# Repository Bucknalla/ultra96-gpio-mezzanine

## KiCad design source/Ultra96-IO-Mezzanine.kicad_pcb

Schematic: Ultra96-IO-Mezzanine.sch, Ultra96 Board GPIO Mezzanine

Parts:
C1, C3: 4.7uF; C_0805_2012Metric
C2, C4: 0.1uF; C_0805_2012Metric
C5, C6, C7, C9: 1uF; C_0805_2012Metric
C8: C_Small; C_0805_2012Metric
D1, D2, D8, D9, D10: LED; LED_0805_2012Metric
D3: SP0503BAHT; SOT-143
D4, D5, D6, D7: D_Schottky; D_0805_2012Metric
H1, H2: MountingHole; Hole_2.5MM
J1, J3: USB_C_Receptacle_USB2.0; USB_C_Receptacle_HRO_TYPE-C-31-M-12
J2: Conn_01x08_Female; PinHeader_1x08_P2.54mm_Vertical
P1: CONN_02X20; PinHeader_2x20_P2.54mm_Vertical
P2: CONN_02X30; 61083-063400LF
P3: CONN_02X20; Socket_Strip_SMD_2x20_Pitch2mm; Mfr Part # F240-1220A0xMUx1
Q1: STL6P3LLH6; TRANS_STL6P3LLH6
R1: 22.1K; R_0805_2012Metric
R2: 47.5K; R_0805_2012Metric
R3, R6, R9, R11, R12, R13: 1K; R_0805_2012Metric
R4, R5: 75R; R_0805_2012Metric
R7: 100K; R_0805_2012Metric
R8: 22K; R_0805_2012Metric
R10: 100; R_0805_2012Metric
SW1: SW_SP3T; SW_SP3T_PCM13
SW2: PWR_BTN; SW_Push_1P1T_NO_Vertical_Wuerth_434133025816
SW3: RST_BTN; SW_Push_1P1T_NO_Vertical_Wuerth_434133025816
U2: CP2102N-A01-GQFN24; QFN-24-1EP_4x4mm_P0.5mm_EP2.6x2.6mm
U3, U5, U6, U7: TXS0108EPW; QFN50P450X350X100-21N
U4: STUSB4500QTR; QFN-24-1EP_4x4mm_P0.5mm_EP2.7x2.7mm

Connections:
+1V8: P3.35, SW1.1, U3.2 (VCCA), U3.10 (OE), U5.2 (VCCA), U5.10 (OE), U6.2 (VCCA), U6.10 (OE), U7.2 (VCCA), U7.10 (OE); also elsewhere on the board
+2V8: C6.1, U4.23 (VREG_2V7)
+3V3: C3.1, C4.1, P1.1, P1.17, R3.1, R4.1, R5.1, R11.1, R12.1, R13.1, SW1.2, U2.5, U2.6, U4.22 (VSYS)
+5V: P1.2, P1.4, P3.37, SW1.4, U2.7; also elsewhere on the board
CC1: D7.1 (K), J1.A5 (CC1), U4.1 (CC1DB), U4.2 (CC1)
CC2: D5.1 (K), J1.B5 (CC2), U4.4 (CC2), U4.5 (CC2DB)
CLK0/CSI0_MCLK: P2.15
CLK1/CSI1_MCLK: P2.17
CSI0_C+: P2.2
CSI0_C-: P2.4
CSI0_D0+: P2.8
CSI0_D0-: P2.10
CSI0_D1+: P2.14
CSI0_D1-: P2.16
CSI0_D2+: P2.20
CSI0_D2-: P2.22
CSI0_D3+: P2.26
CSI0_D3-: P2.28
CSI1_C+: P2.54
CSI1_C-: P2.56
CSI1_D0+: P2.42
CSI1_D0-: P2.44
CSI1_D1+: P2.48
CSI1_D1-: P2.50
D+: D3.4, J3.A6 (D+), J3.B6 (D+), U2.3
D-: D3.3, J3.A7 (D-), J3.B7 (D-), U2.4
DSI_CLK+: P2.21
DSI_CLK-: P2.23
DSI_D0+: P2.27
DSI_D0-: P2.29
DSI_D1+: P2.33
DSI_D1-: P2.35
DSI_D2+: P2.39
DSI_D2-: P2.41
DSI_D3+: P2.45
DSI_D3-: P2.47
GND: C1.2, C2.2, C3.2, C4.2, C5.2, C6.2, C7.2, C9.2, D3.1, D4.2 (A), D5.2 (A), D6.2 (A), D7.2 (A), J1.A1 (GND), J1.A12 (GND), J1.B1 (GND), J1.B12 (GND), J1.S1 (SHIELD), J2.4, J3.A1 (GND), J3.A12 (GND), J3.B1 (GND), J3.B12 (GND), J3.S1 (SHIELD), P1.6, P1.9, P1.14, P1.20, P1.25, P1.30, P1.34, P1.39, P2.6, P2.12, P2.13, P2.18, P2.19, P2.24, P2.25, P2.30, P2.31, P2.37, P2.40, P2.43, P2.46, P2.49, P2.52, P2.55, P2.58, P3.1, P3.2, P3.39, P3.40, R2.1, SW2.1, SW3.1, U2.2, U2.25, U3.11 (GND), U4.10 (GND), U4.12 (ADDR0), U4.13 (ADDR1), U4.25 (GND), U5.11 (GND), U6.11 (GND), U7.11 (GND); also elsewhere on the board
GPIO_A: P3.23, U3.4 (A3); also elsewhere on the board
GPIO_A_RPI: P1.7, U3.17 (B3)
GPIO_B: P3.24, U7.3 (A2); also elsewhere on the board
GPIO_B_RPI: P1.32, U7.18 (B2)
GPIO_C: P3.25, U3.5 (A4); also elsewhere on the board
GPIO_C_RPI: P1.13, U3.16 (B4)
GPIO_D: P3.26, U3.6 (A5); also elsewhere on the board
GPIO_D_RPI: P1.15, U3.15 (B5)
GPIO_E: P3.27, U6.1 (A1); also elsewhere on the board
GPIO_E_RPI: P1.16, U6.20 (B1)
GPIO_F: P3.28, U6.7 (A6); also elsewhere on the board
GPIO_F_RPI: P1.18, U6.14 (B6)
GPIO_G: P3.29, U6.3 (A2); also elsewhere on the board
GPIO_G_RPI: P1.22, U6.18 (B2)
GPIO_H: P3.30, U6.6 (A5); also elsewhere on the board
GPIO_H_RPI: P1.26, U6.15 (B5)
GPIO_I: P3.31, U6.4 (A3); also elsewhere on the board
GPIO_I_RPI: J2.5, P1.29, U6.17 (B3)
GPIO_J: P3.32, U5.4 (A3); also elsewhere on the board
GPIO_J_RPI: J2.6, P1.31, U5.17 (B3)
GPIO_K: P3.33, U6.5 (A4); also elsewhere on the board
GPIO_K_RPI: J2.8, P1.37, U6.16 (B4)
GPIO_L: P3.34, U5.5 (A4); also elsewhere on the board
GPIO_L_RPI: J2.7, P1.33, U5.16 (B4)
HSIC_STR: P2.57
I2C0_SCL: P3.15, U3.3 (A2); also elsewhere on the board
I2C0_SCL_RPI: J2.1, P1.5, U3.18 (B2), U4.7 (SCL)
I2C0_SDA: P3.17, U3.1 (A1); also elsewhere on the board
I2C0_SDA_RPI: J2.2, P1.3, U3.20 (B1), U4.8 (SDA)
I2C1_SCL: P3.19, U5.3 (A2); also elsewhere on the board
I2C1_SCL_RPI: P1.28, U5.18 (B2)
I2C1_SDA: P3.21, U5.1 (A1); also elsewhere on the board
I2C1_SDA_RPI: P1.27, U5.20 (B1)
I2C2_SCL: P2.32
I2C2_SDA: P2.34
I2C3_SCL: P2.36
I2C3_SDA: P2.38
unnamed: C7.1, U4.21 (VREG_1V2)
unnamed: C8.2, R10.1
unnamed: D1.1, U2.14
unnamed: D1.2, R5.2
unnamed: D2.1, U2.13
unnamed: D2.2, R4.2
unnamed: D8.1, U4.15 (GPIO)
unnamed: D8.2, R11.2
unnamed: D9.1, U4.20 (POWER_OK2)
unnamed: D9.2, R12.2
unnamed: D10.1, U4.14 (POWER_OK3)
unnamed: D10.2, R13.2
unnamed: Q1.1, Q1.2, Q1.3, R7.1
unnamed: Q1.4, R7.2, R8.1, R10.2
unnamed: R1.2, R2.2, U2.8
unnamed: R3.2, U2.9
unnamed: R6.1, U4.18 (VBUS_VS_DISCH)
unnamed: R8.2, U4.16 (VBUS_EN_SNK)
unnamed: R9.2, U4.9 (DISCH)
PCM_CLK: P3.18, U5.9 (A8); also elsewhere on the board
PCM_CLK_RPI: P1.12, U5.12 (B8)
PCM_DI: P3.22, U5.7 (A6); also elsewhere on the board
PCM_DI_RPI: P1.38, U5.14 (B6)
PCM_DO: P3.20, U5.8 (A7); also elsewhere on the board
PCM_DO_RPI: P1.40, U5.13 (B7)
PCM_FS: P3.16, U5.6 (A5); also elsewhere on the board
PCM_FS_RPI: P1.35, U5.15 (B5)
PWR_BTN_N: P3.4, SW2.2; also elsewhere on the board
RST_BTN_N: P3.6, SW3.2; also elsewhere on the board
SD_CMD/SPI1_DIN: P2.11
SD_DAT0/SPI1_DOUT: P2.1
SD_DAT1: P2.3
SD_DAT2: P2.5
SD_DAT3/SPI1_CS: P2.7
SD_SCLK/SPI1_SCLK: P2.9
SPIO_CS: P3.12, U7.1 (A1); also elsewhere on the board
SPIO_CS_RPI: P1.24, U7.20 (B1)
SPIO_DIN: P3.10, U3.8 (A7); also elsewhere on the board
SPIO_DIN_RPI: P1.21, U3.13 (B7)
SPIO_DOUT: P3.14, U3.7 (A6); also elsewhere on the board
SPIO_DOUT_RPI: P1.19, U3.14 (B6)
SPIO_SCL: P3.8, U3.9 (A8); also elsewhere on the board
SPIO_SCL_RPI: P1.23, U3.12 (B8)
SYS_DCIN: C8.1, D4.1 (K), P3.36, P3.38, Q1.5_8, R9.1; also elsewhere on the board
UART0_CTS: P3.3, U7.6 (A5); also elsewhere on the board
UART0_CTS_O: U2.19, U7.15 (B5)
UART0_RTS: P3.9, U7.7 (A6); also elsewhere on the board
UART0_RTS_O: U2.18, U7.14 (B6)
UART0_RX: P3.7, U7.5 (A4); also elsewhere on the board
UART0_RX_O: U2.21, U7.16 (B4)
UART0_TX: P3.5, U7.4 (A3); also elsewhere on the board
UART0_TX_O: U2.20, U7.17 (B3)
UART1_RX: P3.13, U6.9 (A8); also elsewhere on the board
UART1_RX_RPI: P1.10, U6.12 (B8)
UART1_TX: P3.11, U6.8 (A7); also elsewhere on the board
UART1_TX_RPI: P1.8, U6.13 (B7)
USB_D+: P2.51
USB_D-: P2.53
VBUS: C1.1, C2.1, D3.2, J3.A4 (VBUS), J3.A9 (VBUS), J3.B4 (VBUS), J3.B9 (VBUS), R1.1
VBUS_PWR: C5.1, C9.1, D6.1 (K), J1.A4 (VBUS), J1.A9 (VBUS), J1.B4 (VBUS), J1.B9 (VBUS), R6.2, U4.24 (VDD)
VCCB: J2.3, SW1.3, U3.19 (VCCB), U5.19 (VCCB), U6.19 (VCCB), U7.19 (VCCB)

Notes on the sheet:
Top Side Socket Strip
Bottom Side HS Connector
RPi Header
Level Shifters
Power Rails
Lepton Header
Voltage Toggle
USB PD
USB to UART Converter
Buttons
USB PD Connector
USB to Uart Connector

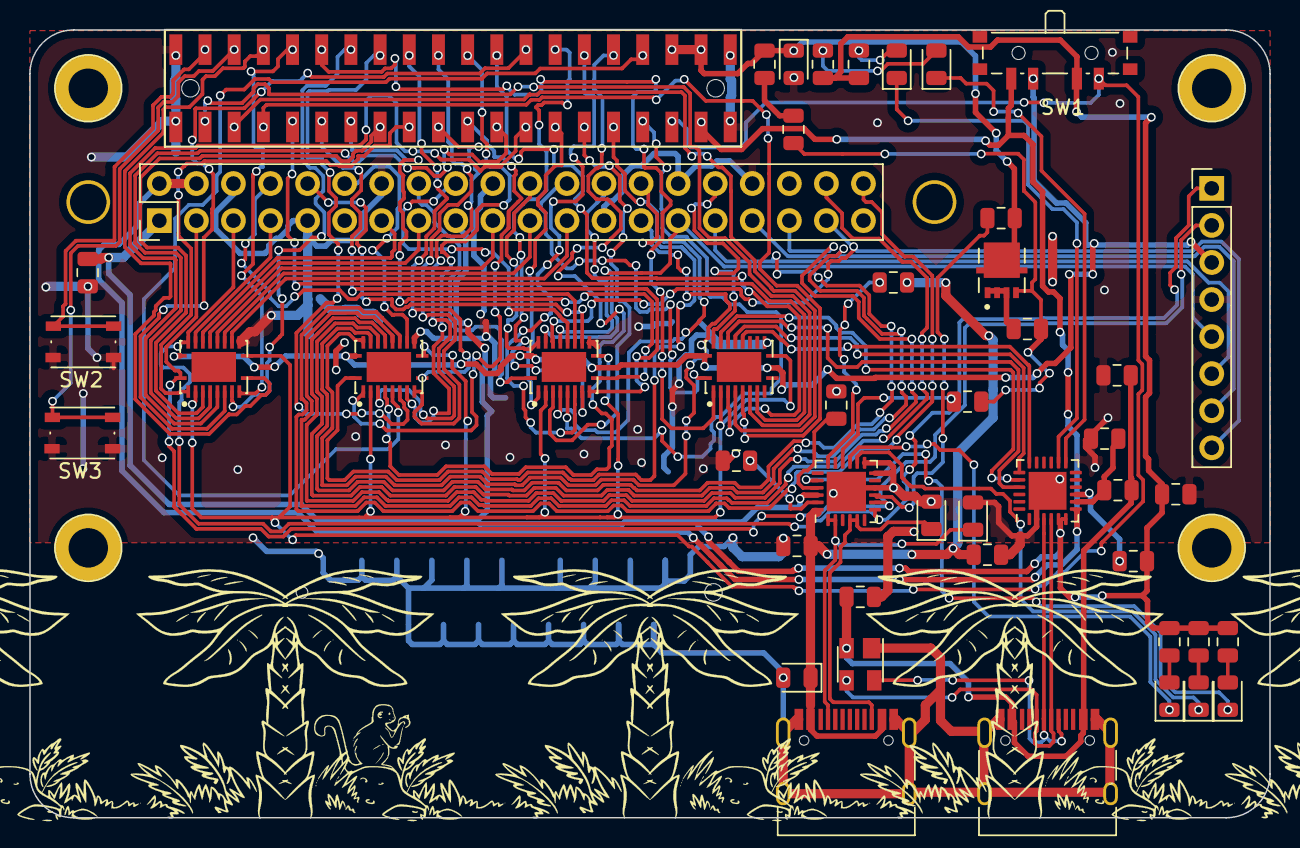
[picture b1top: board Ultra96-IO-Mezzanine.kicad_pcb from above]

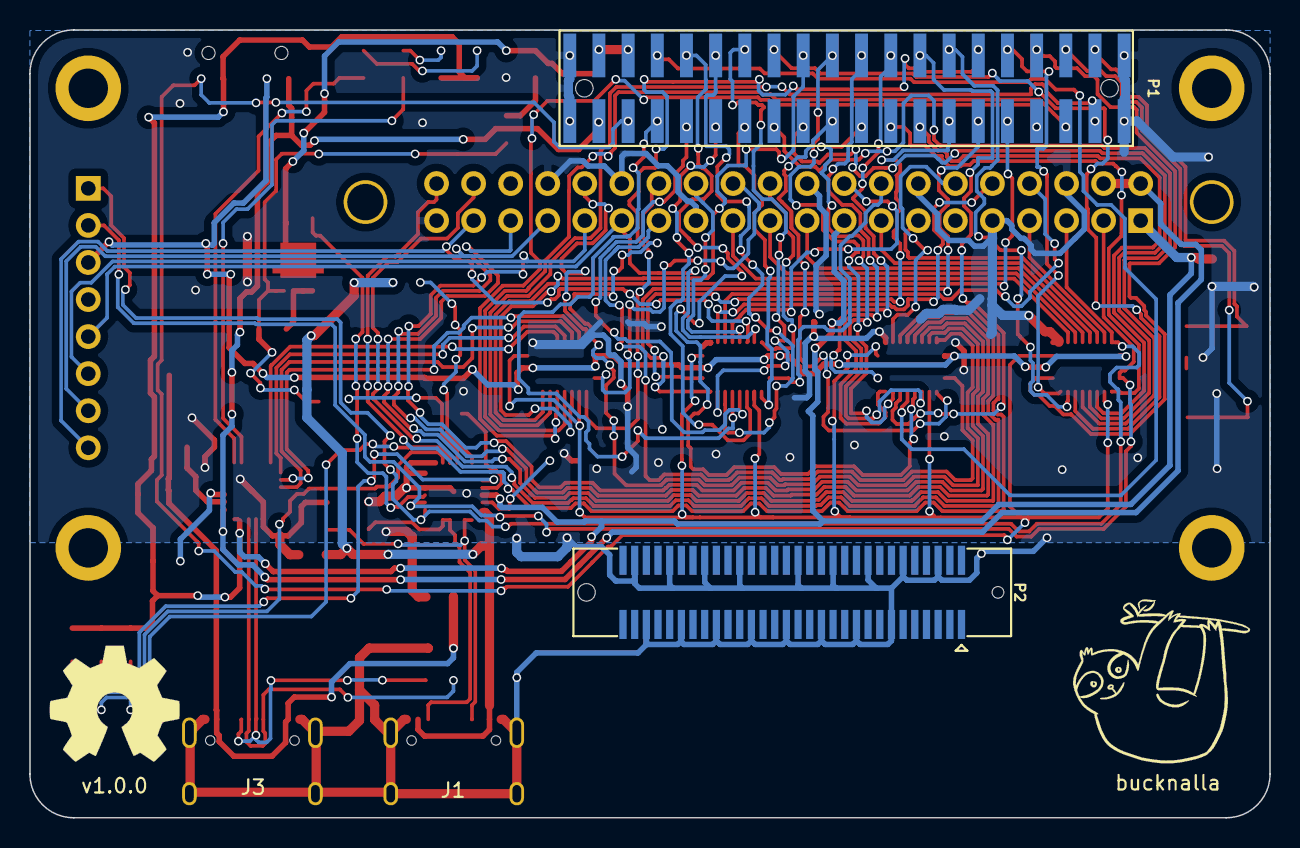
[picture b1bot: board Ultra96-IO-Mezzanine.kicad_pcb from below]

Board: 2 copper layers, 85.0 x 54.0 mm, 51 parts (2 on the bottom side), 94 nets.

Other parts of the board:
P1#2: CONN_02X20; Pin_Header_SMD_2x20_Pitch2mm

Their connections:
+1V8: P1#2.35; also elsewhere on the board
+5V: P1#2.37; also elsewhere on the board
GND: P1#2.1, P1#2.2, P1#2.39, P1#2.40; also elsewhere on the board
GPIO_A: P1#2.23; also elsewhere on the board
GPIO_B: P1#2.24; also elsewhere on the board
GPIO_C: P1#2.25; also elsewhere on the board
GPIO_D: P1#2.26; also elsewhere on the board
GPIO_E: P1#2.27; also elsewhere on the board
GPIO_F: P1#2.28; also elsewhere on the board
GPIO_G: P1#2.29; also elsewhere on the board
GPIO_H: P1#2.30; also elsewhere on the board
GPIO_I: P1#2.31; also elsewhere on the board
GPIO_J: P1#2.32; also elsewhere on the board
GPIO_K: P1#2.33; also elsewhere on the board
GPIO_L: P1#2.34; also elsewhere on the board
I2C0_SCL: P1#2.15; also elsewhere on the board
I2C0_SDA: P1#2.17; also elsewhere on the board
I2C1_SCL: P1#2.19; also elsewhere on the board
I2C1_SDA: P1#2.21; also elsewhere on the board
PCM_CLK: P1#2.18; also elsewhere on the board
PCM_DI: P1#2.22; also elsewhere on the board
PCM_DO: P1#2.20; also elsewhere on the board
PCM_FS: P1#2.16; also elsewhere on the board
PWR_BTN_N: P1#2.4; also elsewhere on the board
RST_BTN_N: P1#2.6; also elsewhere on the board
SPIO_CS: P1#2.12; also elsewhere on the board
SPIO_DIN: P1#2.10; also elsewhere on the board
SPIO_DOUT: P1#2.14; also elsewhere on the board
SPIO_SCL: P1#2.8; also elsewhere on the board
SYS_DCIN: P1#2.36, P1#2.38; also elsewhere on the board
UART0_CTS: P1#2.3; also elsewhere on the board
UART0_RTS: P1#2.9; also elsewhere on the board
UART0_RX: P1#2.7; also elsewhere on the board
UART0_TX: P1#2.5; also elsewhere on the board
UART1_RX: P1#2.13; also elsewhere on the board
UART1_TX: P1#2.11; also elsewhere on the board

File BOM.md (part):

|Ref|Value                  |Footprint                                                     |Datasheet                                                                                                    |Manufacturer|Vendor|
|---|-----------------------|--------------------------------------------------------------|-------------------------------------------------------------------------------------------------------------|------------|------|
|C1 |4.7uF                  |Capacitor_SMD:C_0805_2012Metric                               |~                                                                                                            |            |      |
|C2 |0.1uF                  |Capacitor_SMD:C_0805_2012Metric                               |~                                                                                                            |            |      |
|C3 |4.7uF                  |Capacitor_SMD:C_0805_2012Metric                               |~                                                                                                            |            |      |
|C4 |0.1uF                  |Capacitor_SMD:C_0805_2012Metric                               |~                                                                                                            |            |      |
|C5 |1uF                    |Capacitor_SMD:C_0805_2012Metric                               |~                                                                                                            |            |      |
|C6 |1uF                    |Capacitor_SMD:C_0805_2012Metric                               |~                                                                                                            |            |      |
|C7 |1uF                    |Capacitor_SMD:C_0805_2012Metric                               |~                                                                                                            |            |      |
|C8 |C_Small                |Capacitor_SMD:C_0805_2012Metric                               |~                                                                                                            |            |      |
|C9 |C_Small                |Capacitor_SMD:C_0805_2012Metric                               |~                                                                                                            |            |      |
|D1 |LED                    |LED_SMD:LED_0805_2012Metric                                   |~                                                                                                            |            |      |
|D2 |LED                    |LED_SMD:LED_0805_2012Metric                                   |~                                                                                                            |            |      |
|D3 |SP0503BAHT             |Package_TO_SOT_SMD:SOT-143                                    |http://www.littelfuse.com/~/media/files/littelfuse/technical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|            |      |
|D4 |D_Schottky             |Diode_SMD:D_0805_2012Metric                                   |~                                                                                                            |            |      |
|D5 |D_Schottky             |Diode_SMD:D_0805_2012Metric                                   |~                                                                                                            |            |      |
|D6 |D_Schottky             |Diode_SMD:D_0805_2012Metric                                   |~                                                                                                            |            |      |
|D7 |D_Schottky             |Diode_SMD:D_0805_2012Metric                                   |~                                                                                                            |            |      |
|D8 |LED                    |LED_SMD:LED_0805_2012Metric                                   |~                                                                                                            |            |      |
|D9 |LED                    |LED_SMD:LED_0805_2012Metric                                   |~                                                                                                            |            |      |
|D10|LED                    |LED_SMD:LED_0805_2012Metric                                   |~                                                                                                            |            |      |
|H1 |MountingHole           |96boards:Hole_2.5MM                                           |~                                                                                                            |            |      |
|H2 |MountingHole           |96boards:Hole_2.5MM                                           |~                                                                                                            |            |      |
|J1 |USB_C_Receptacle_USB2.0|Connector_USB:USB_C_Receptacle_HRO_TYPE-C-31-M-12             |https://www.usb.org/sites/default/files/documents/usb_type-c.zip                                             |            |      |
|J2 |Conn_01x08_Female      |Connector_PinHeader_2.54mm:PinHeader_1x08_P2.54mm_Vertical    |~                                                                                                            |            |      |
|J3 |USB_C_Receptacle_USB2.0|Connector_USB:USB_C_Receptacle_HRO_TYPE-C-31-M-12             |https://www.usb.org/sites/default/files/documents/usb_type-c.zip                                             |            |      |
|P1 |CONN_02X20             |Connector_PinHeader_2.54mm:PinHeader_2x20_P2.54mm_Vertical    |                                                                                                             |            |      |
|P2 |CONN_02X30             |96boards:61083-063400LF                                       |http://portal.fciconnect.com/Comergent/fci/drawing/61083.pdf                                                 |            |      |
|P3 |CONN_02X20             |96boards:Socket_Strip_SMD_2x20_Pitch2mm                       |                                                                                                             |            |      |
|Q1 |STL6P3LLH6             |snapeda:TRANS_STL6P3LLH6                                      |ST Microelectronics                                                                                          |            |      |
|R1 |22.1K                  |Resistor_SMD:R_0805_2012Metric                                |~                                                                                                            |            |      |
|R2 |47.5K                  |Resistor_SMD:R_0805_2012Metric                                |~                                                                                                            |            |      |
|R3 |1K                     |Resistor_SMD:R_0805_2012Metric                                |~                                                                                                            |            |      |
|R4 |75R                    |Resistor_SMD:R_0805_2012Metric                                |~                                                                                                            |            |      |
|R5 |75R                    |Resistor_SMD:R_0805_2012Metric                                |~                                                                                                            |            |      |
|R6 |1K                     |Resistor_SMD:R_0805_2012Metric                                |~                                                                                                            |            |      |
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
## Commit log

2020-07-21 highspeed connector
2020-07-24 Progress
2020-08-14 Further work on PCB
2020-08-18 Added TXS0108
2020-08-19 Started wiring
2020-08-19 Mostly routed now
2020-08-19 3 left
2020-08-20 All levelshifters routed
2020-08-20 Finished routing
2020-08-20 Tidying
2020-08-21 Further tidying
2020-08-21 Removed part names
2020-08-25 Tidy up schematic
2020-11-21 Storing history
2020-11-21 Updated gitignore
2020-11-21 .gitignore is now working
2020-11-21 prototyped version
2020-11-22 tweaks to file system
2020-11-23 maybe working now?
2020-11-23 Updated workflows and fixed DRC issues
2020-11-23 Fixed lib issue
2020-11-23 tweak
2020-11-23 testing CI
2020-11-23 fixing config
2020-11-23 testing CI tweak
2020-11-23 testing CI again
2020-11-23 Testing things
